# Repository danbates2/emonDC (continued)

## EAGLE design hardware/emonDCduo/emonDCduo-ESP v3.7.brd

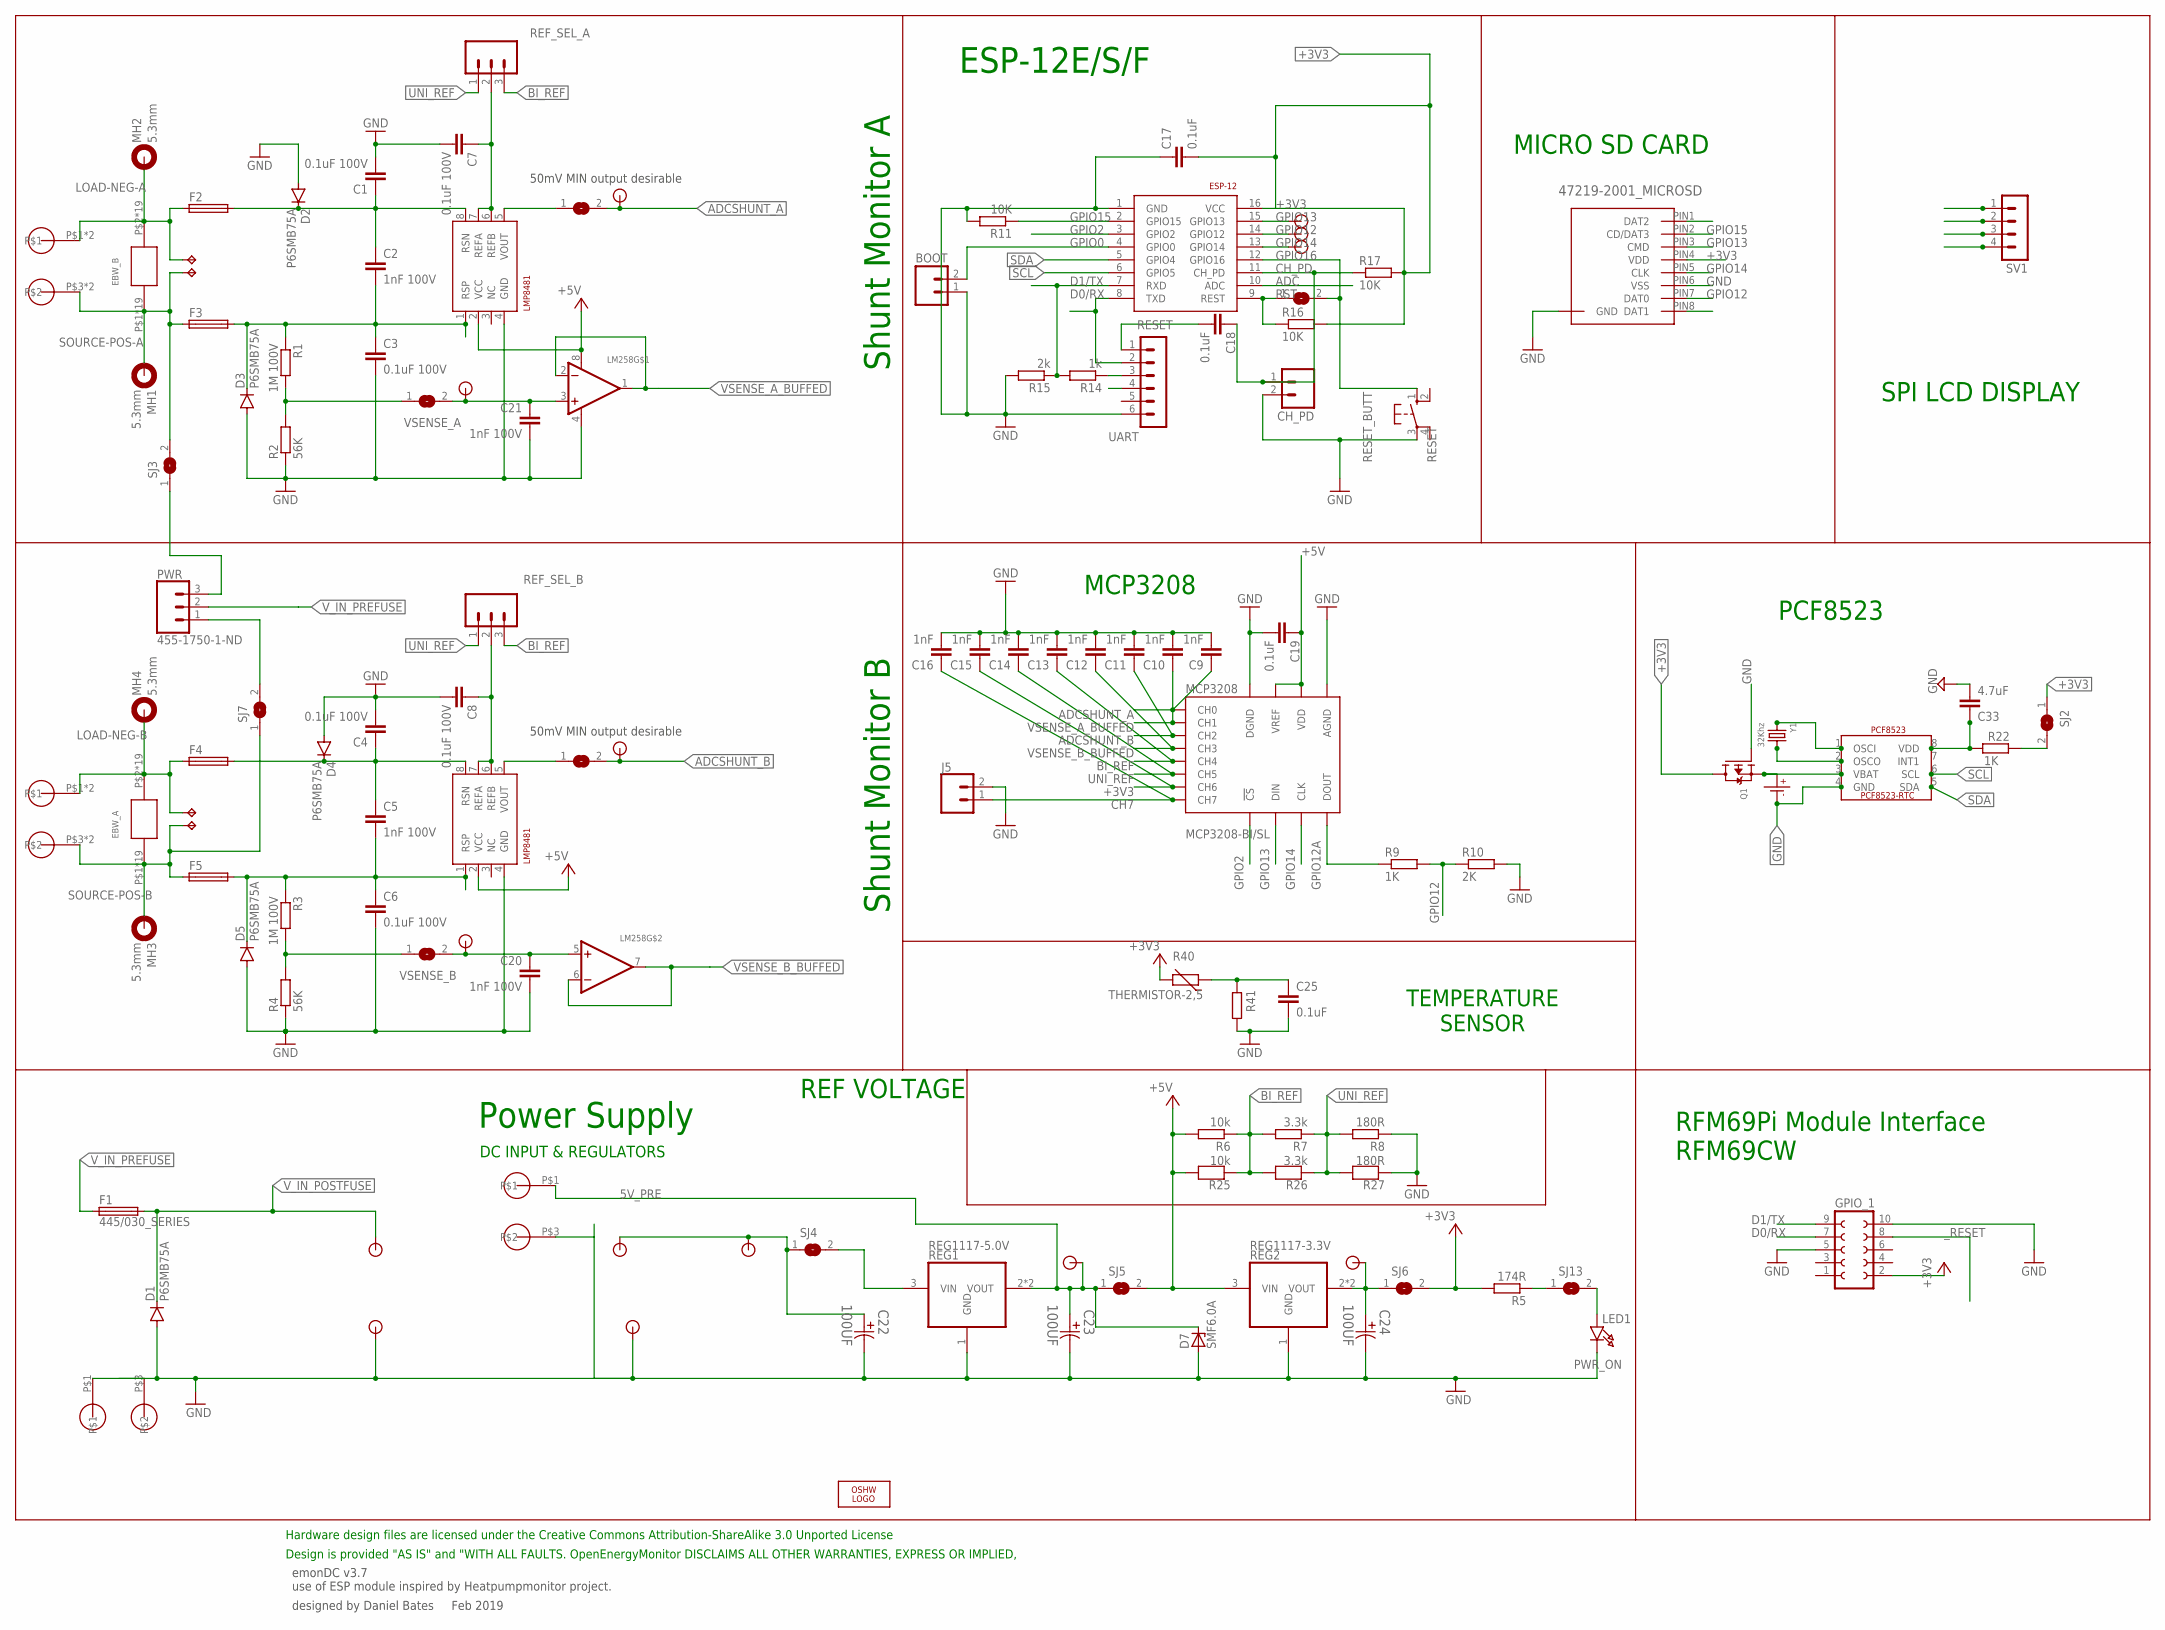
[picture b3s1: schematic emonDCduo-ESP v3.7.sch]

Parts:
BOOT: M02PTH; 1X02
C1, C3, C4, C6, C7, C8: 0.1uF 100V; C0805; MPN C1608X7S2A104K080AB
C2, C5, C20, C21: 1nF 100V; C0805; MPN C1608X7S2A104K080AB
C9, C10, C11, C12, C13, C14, C15, C16: 1nF; C0603
C17, C19, C25: 0.1uF; C0805
C18: 0.1uF; C0603
C22, C23, C24: 100UF; CAPAE530X610N
C33: 4.7uF; C0805
CH_PD: M02PTH; 1X02
CR1220: CR1220SMD; MPN Harwin S8411-45R
D1: P6SMB75A; DO214AA
D2, D3, D4, D5: P6SMB75A; SMB
D7: SMF6.0A; SOD123F
EBW_A: EBW_SERIES_15.2MM
EBW_B: EBW_SERIES_15.2MM
ESP-12: ESP8266_ESP-12; ESP8266-ESP12
F1: 445/030_SERIES; 445/030_SERIES_LITTELFUSE
F2, F3, F4, F5: TR5
GPIO_1: FE05-2_RFM69PI_OUTLINERFM69PI; FE05-2_RFM69PI_OULTINE
J5: CONN_02; 1X02
LED1: PWR_ON; CHIPLED_1206
LM258: LM358; SOIC8_150MIL
LOGO1: OSHW_LOGO_6MILX0200-NT; OSHW_6X200_NOTEXT
MCP3208: MCP3208-BI/SL; SOIC16
MH1, MH2, MH3, MH4: 5.3mm; 5,3//11-PAD
MICRO_SD: 47219-2001_MICROSD
MOUNT_10.16_A, MOUNT_10.16_B: MOLEX_39970-003; 2/10,16
PCF8523: PCF8523_RTC; SOIC_8
PWR: 455-1750-1-ND; 1X03
Q1: MOSFET-P; SOT23-R
R1, R3: 1M 100V; 0207/2V; MPN MCMF006FF1004A50
R2, R4: 56K; 0207/2V; MPN MCMF006FF7502A50
R5: 174R; R0603
R6: 10k; 0207/10
R7: 3.3k; 0207/10
R8: 180R; 0207/10
R9: 1K; R0603; MPN MCWR06X5901FTL
R10: 2K; R0603; MPN MCWR06X5901FTL
R11, R16, R17: 10K; R0603
R14: 1k; R0603
R15: 2k; R0603
R22: 1K; R0603
R25: 10k; 0603
R26: 3.3k; 0603
R27: 180R; 0603
R40: THERMISTOR-2,5; RS-2,5
R41: R-EU_0207/2V; 0207/2V
REF_SEL_A: 455-1750-1-ND; 1X03; MPN 2212S-02SG-85
REF_SEL_B: 455-1750-1-ND; 1X03; MPN 2212S-02SG-85
REG1: REG1117-5.0V; SOT223; MPN REG1117-5.0
REG2: REG1117-3.3V; SOT223; MPN REG1117-3.3
RESET: RESET_BUTT; B3F-10XX
SHUNTMON-A: LMP8481; S-PDSO-G08; MPN LMP8481MME-S/NOPB
SHUNTMON-B: LMP8481; S-PDSO-G08; MPN LMP8481MME-H/NOPB
SJ1, SJ2, SJ4, SJ5, SJ6, SJ8, SJ9, SJ10, SJ11, SJ13: SOLDERJUMPERCLOSED; SOLDERJUMPER_CLOSEDWIRE
SJ3, SJ7: SJ
SV1: MA04-1; MPN 2212S-04SG-85
TP8, TP9, TP10, TP11: TPPAD1-13Y; P1-13Y
U$1, U$4, U$5, U$6, U$7, U$8, U$9, U$14, U$15, U$16: TP0.8MM; TP0.8
U$2, U$3, U$10, U$11: 2212S-02SG-85; TP0.8_X2
U$12, U$13: 5MMBLOCK; 2/5.08
UART: UART; MA06-1
Y1: 32Khz; CRYSTAL_8X3.8

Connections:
3.3V_PRE: C24.1, REG2.2 (VOUT), REG2.4 (VOUT), SJ6.1, U$8.P$1
5V_PRE: C23.1, D7.C, REG1.2 (VOUT), REG1.4 (VOUT), SJ5.1, U$7.P$1, U$12.P$1
6.5V: REG1.3 (VIN), SJ4.2
+3V3: C15.1, C17.2, ESP-12.16 (VCC), GPIO_1.2, MCP3208.7 (CH6), MICRO_SD.PIN4 (VDD), Q1.3 (D), R5.2, R16.2, R17.2, R40.2, SJ2.1, SJ6.2, SV1.3
+5V: C19.1, LM258.8 (V+), MCP3208.15 (VREF), MCP3208.16 (VDD), R6.2, R25.2, REG2.3 (VIN), SHUNTMON-A.2 (VCC), SHUNTMON-B.2 (VCC), SJ5.2, UART.4
ADC: C25.1, ESP-12.10 (ADC), R40.1, R41.2
ADCSHUNT_A: C9.1, MCP3208.1 (CH0), SJ11.2, U$6.P$1
ADCSHUNT_B: C11.1, MCP3208.3 (CH2), SJ10.2, U$5.P$1
BI_REF: C13.1, MCP3208.5 (CH4), R6.1, R7.2, R25.1, R26.2, REF_SEL_A.3, REF_SEL_B.3
CH7: C16.1, J5.1, MCP3208.8 (CH7)
CH_PD: C18.1, CH_PD.1, ESP-12.11 (CH_PD), R17.1
D0/RX: ESP-12.8 (TXD), GPIO_1.7, UART.2
D1/TX: ESP-12.7 (RXD), GPIO_1.9, R14.2, R15.1
GND: BOOT.1, C1.2, C3.2, C4.2, C6.2, C7.2, C8.2, C9.2, C10.2, C11.2, C12.2, C13.2, C14.2, C15.2, C16.2, C17.1, C19.2, C20.2, C21.2, C22.2, C23.2, C24.2, C25.2, C33.2, CH_PD.2, CR1220.P- (P$-), D1.A, D2.A, D3.A, D4.A, D5.A, D7.A, ESP-12.1 (GND), GPIO_1.5, GPIO_1.10, J5.2, LED1.C, LM258.4 (V-), MCP3208.9 (DGND), MCP3208.14 (AGND), MICRO_SD.P$1 (GND), MICRO_SD.P$2 (GND), MICRO_SD.P$3 (GND), MICRO_SD.P$4 (GND), MICRO_SD.PIN6 (VSS), PCF8523.4 (GND), Q1.1 (G), R2.1, R4.1, R8.1, R10.2, R11.2, R15.2, R27.1, R41.1, REG1.1 (GND), REG2.1 (GND), RESET.3, SHUNTMON-A.4 (GND), SHUNTMON-B.4 (GND), SV1.4, U$3.P$1, U$3.P$2, U$11.P$1, U$11.P$2, U$12.P$3, U$13.P$1, U$13.P$3, UART.6
GPIO0: BOOT.2, ESP-12.4 (GPIO0)
GPIO2: ESP-12.3 (GPIO2), MCP3208.10 (!CS)
GPIO12: ESP-12.14 (GPIO12), MICRO_SD.PIN7 (DAT0), R9.2, R10.1, U$14.P$1
GPIO12A: MCP3208.12 (DOUT), R9.1
GPIO13: ESP-12.15 (GPIO13), MCP3208.11 (DIN), MICRO_SD.PIN3 (CMD), U$15.P$1
GPIO14: ESP-12.13 (GPIO14), MCP3208.13 (CLK), MICRO_SD.PIN5 (CLK), U$16.P$1
GPIO15: ESP-12.2 (GPIO15), MICRO_SD.PIN2 (CD/DAT3), R11.1
GPIO16: ESP-12.12 (GPIO16), RESET.1 (S), SJ1.2
LOAD-NEG-A: EBW_B.P$2, EBW_B.P$18, EBW_B.P$19, EBW_B.P$20, EBW_B.P$21, EBW_B.P$22, EBW_B.P$23, EBW_B.P$24, EBW_B.P$25, EBW_B.P$26, EBW_B.P$27, EBW_B.P$28, EBW_B.P$29, EBW_B.P$30, EBW_B.P$31, EBW_B.P$32, EBW_B.P$36, EBW_B.P$37, EBW_B.P$38, F2.1, MH2.B5,5, MOUNT_10.16_A.P$1, MOUNT_10.16_A.P$2, TP11.TP
LOAD-NEG-A_T: C1.1, C2.1, D2.C, F2.2, SHUNTMON-A.8 (RSN)
LOAD-NEG-B: EBW_A.P$2, EBW_A.P$18, EBW_A.P$19, EBW_A.P$20, EBW_A.P$21, EBW_A.P$22, EBW_A.P$23, EBW_A.P$24, EBW_A.P$25, EBW_A.P$26, EBW_A.P$27, EBW_A.P$28, EBW_A.P$29, EBW_A.P$30, EBW_A.P$31, EBW_A.P$32, EBW_A.P$36, EBW_A.P$37, EBW_A.P$38, F4.1, MH4.B5,5, MOUNT_10.16_B.P$1, MOUNT_10.16_B.P$2, TP9.TP
LOAD-NEG-B_T: C4.1, C5.1, D4.C, F4.2, SHUNTMON-B.8 (RSN)
unnamed: PWR.3, SJ3.1
unnamed: PWR.1, SJ7.2
unnamed: R5.1, SJ13.1
unnamed: LED1.A, SJ13.2
unnamed: SHUNTMON-B.5 (VOUT), SJ10.1
unnamed: SHUNTMON-A.5 (VOUT), SJ11.1
unnamed: R14.1, UART.3
unnamed: PCF8523.2 (OSCO), Y1.P$4 (2)
unnamed: PCF8523.1 (OSCI), Y1.P$1 (1)
REF_A_INPUT: C7.1, REF_SEL_A.2, SHUNTMON-A.6 (REFB), SHUNTMON-A.7 (REFA)
REF_B_INPUT: C8.1, REF_SEL_B.2, SHUNTMON-B.6 (REFB), SHUNTMON-B.7 (REFA)
RESET: C18.2, UART.1
RST: ESP-12.9 (REST), R16.1, SJ1.1
SCL: ESP-12.6 (GPIO5), PCF8523.6 (SCL), SV1.2
SDA: ESP-12.5 (GPIO4), PCF8523.5 (SDA), SV1.1
SOURCE-POS-A: EBW_B.P$1, EBW_B.P$3, EBW_B.P$4, EBW_B.P$5, EBW_B.P$6, EBW_B.P$7, EBW_B.P$8, EBW_B.P$9, EBW_B.P$10, EBW_B.P$11, EBW_B.P$12, EBW_B.P$13, EBW_B.P$14, EBW_B.P$15, EBW_B.P$16, EBW_B.P$17, EBW_B.P$33, EBW_B.P$34, EBW_B.P$35, F3.1, MH1.B5,5, MOUNT_10.16_A.P$3, MOUNT_10.16_A.P$4, SJ3.2, TP10.TP
SOURCE-POS-A_T: C2.2, C3.1, D3.C, F3.2, R1.1, SHUNTMON-A.1 (RSP)
SOURCE-POS-B: EBW_A.P$1, EBW_A.P$3, EBW_A.P$4, EBW_A.P$5, EBW_A.P$6, EBW_A.P$7, EBW_A.P$8, EBW_A.P$9, EBW_A.P$10, EBW_A.P$11, EBW_A.P$12, EBW_A.P$13, EBW_A.P$14, EBW_A.P$15, EBW_A.P$16, EBW_A.P$17, EBW_A.P$33, EBW_A.P$34, EBW_A.P$35, F5.1, MH3.B5,5, MOUNT_10.16_B.P$3, MOUNT_10.16_B.P$4, SJ7.1, TP8.TP
SOURCE-POS-B_T: C5.2, C6.1, D5.C, F5.2, R3.1, SHUNTMON-B.1 (RSP)
UNI_REF: C14.1, MCP3208.6 (CH5), R7.1, R8.2, R26.1, R27.2, REF_SEL_A.1, REF_SEL_B.1
VBAT: CR1220.P+ (P$+), PCF8523.3 (VBAT), Q1.2 (S)
VDD_PCF: C33.1, PCF8523.8 (VDD), R22.1
VDD_RTC_POSTJUMPER: R22.2, SJ2.2
VOUT_POST_SWITCHING: C22.1, SJ4.1, U$9.P$1, U$10.P$1, U$10.P$2
VSENSE_A: R1.2, R2.2, SJ8.1
VSENSE_A_BUFFED: C10.1, LM258.1 (OUT), LM258.2 (-IN), MCP3208.2 (CH1)
VSENSE_A_TP: C21.1, LM258.3 (+IN), SJ8.2, U$1.P$1
VSENSE_B: R3.2, R4.2, SJ9.1
VSENSE_B_BUFFED: C12.1, LM258.6 (-IN), LM258.7 (OUT), MCP3208.4 (CH3)
VSENSE_B_TP: C20.1, LM258.5 (+IN), SJ9.2, U$4.P$1
V_IN_POSTFUSE: D1.C, F1.P$3 (2), F1.P$4 (2), U$2.P$1, U$2.P$2
V_IN_PREFUSE: F1.P$1 (1), F1.P$2 (1), PWR.2
_RESET: GPIO_1.8

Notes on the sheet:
emonDC v3.7 use of ESP module inspired by Heatpumpmonitor project.
designed by Daniel Bates Feb 2019
Power Supply
Design is provided "AS IS" and "WITH ALL FAULTS. OpenEnergyMonitor DISCLAIMS ALL OTHER WARRANTIES, EXPRESS OR IMPLIED,
Hardware design files are licensed under the Creative Commons Attribution-ShareAlike 3.0 Unported License
DC INPUT & REGULATORS
Shunt Monitor B
Shunt Monitor A
ESP-12E/S/F
MICRO SD CARD
RFM69Pi Module Interface RFM69CW
MCP3208
PCF8523
SPI LCD DISPLAY
TEMPERATURE SENSOR
50mV MIN output desirable
REF VOLTAGE

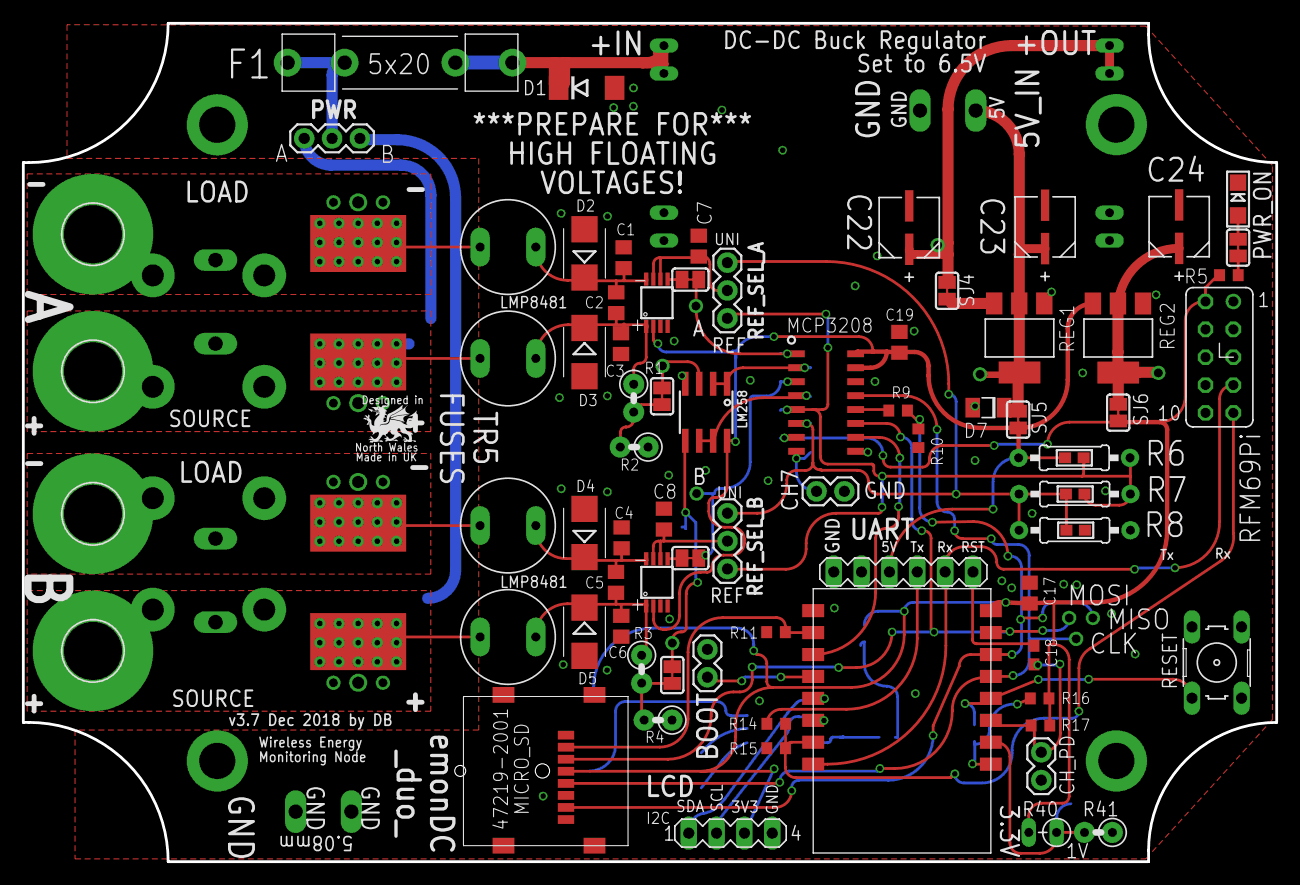
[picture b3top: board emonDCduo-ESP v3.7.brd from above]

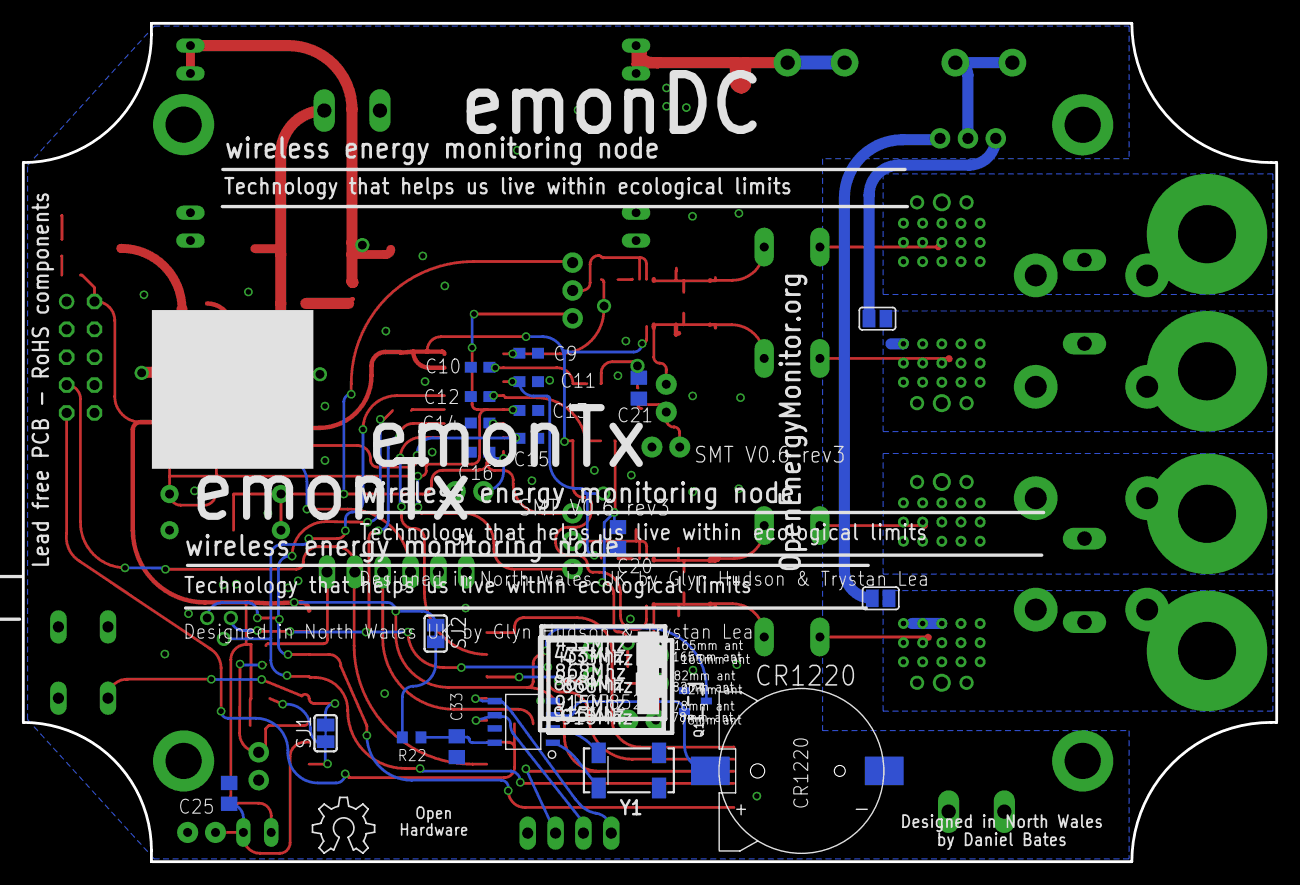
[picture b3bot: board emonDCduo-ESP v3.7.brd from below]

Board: 2 copper layers, 114.3 x 76.5 mm, 122 parts (24 on the bottom side), 58 nets.
